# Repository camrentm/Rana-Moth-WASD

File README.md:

# The Rana Labs Moth (WASD Version)

WASD version of [Rana Labs'](https://github.com/rana-sylvatica) Moth, a foldable leverless controller.

<div style="display: flex; gap: 10px;">

</div>

---

## Components

I printed the entire shell and hinges in **Bambu Lab Matte PLA** (any PLA should work, though build quality feel may vary).

- **Mainboard:** RP2040 integrated directly onto the left custom PCB. The right side connects via ribbon cable.
- **Switches:** Any Kailh Choc low-profile switch. Must be low-profile (standard height switches won't fit).
- **USB-C:** [QuRB](https://github.com/rana-sylvatica/rana-tadpole/tree/main/PCBs/Breakout%20Board%20(QuRB)) by [Quark Works](https://github.com/quark-works) and Rana Labs, a USB-C breakout board with a ribbon cable port for solderless assembly.
- **Hardware:** M2 and M3 screws only. You'll need ten M3 heat inserts for the backplates, twelve M3×5/6mm bolts for the backplates and QuRB, and eight M2×4mm bolts for the mainboards.

---

## Assembly

The custom PCB eliminates all handwiring. The only soldering required is installing the hotswap sockets for the Choc switches.

The two halves connect via a 20-pin 0.5mm pitch ribbon cable. The QuRB connects to the left board via a 12-pin 0.5mm pitch ribbon cable for the USB-C port.

---

## Firmware

This build runs a custom fork of HayBox configured for the Moth layout. Find it at [camrentm/HayBox-Rana-Moth](https://github.com/camrentm/HayBox-Rana-Moth).

---

## Magnets

Strong magnets are essential since they're working against the spring force of every switch.

- **Size:** 6×3mm Neodymium, stacked 2 high per hole
- **Count:** 10 holes × 2 magnets = **20 magnets total**

The snap when closing is very satisfying and holds the Moth securely folded.

---

## Prism Ergonomic Mode

In the reverse-folded position, a lip on each hinge piece stops the wings from overfolding and creates a clean resting angle. The rounded hinge backs add friction to keep the Moth rigid in this position.

You can edit the lip width in the hinge model to adjust the fold angle to your preference.

---

## Notes

- **Button fit:** Buttons must sit flush with the face when depressed, or the halves won't close cleanly. Strong magnets may compensate for minor protrusion.
- **Hinge pin slot:** Left open in this design. The friction fit holds without caps, and it makes intentional pin removal much easier.

---

## Files

| Folder | Contents |
|--------|----------|
| `Shell/` | Top panels and backplates (STEP) |
| `Hinge and Buttons/` | Hinge upper/lower, hinge pin, and keycap models (STEP) |
| `Moth PCB/` | KiCad PCB project, schematics, and fabrication files |
| `DXF/` | PCB outlines and hole patterns |
| `Images/` | Build photos |

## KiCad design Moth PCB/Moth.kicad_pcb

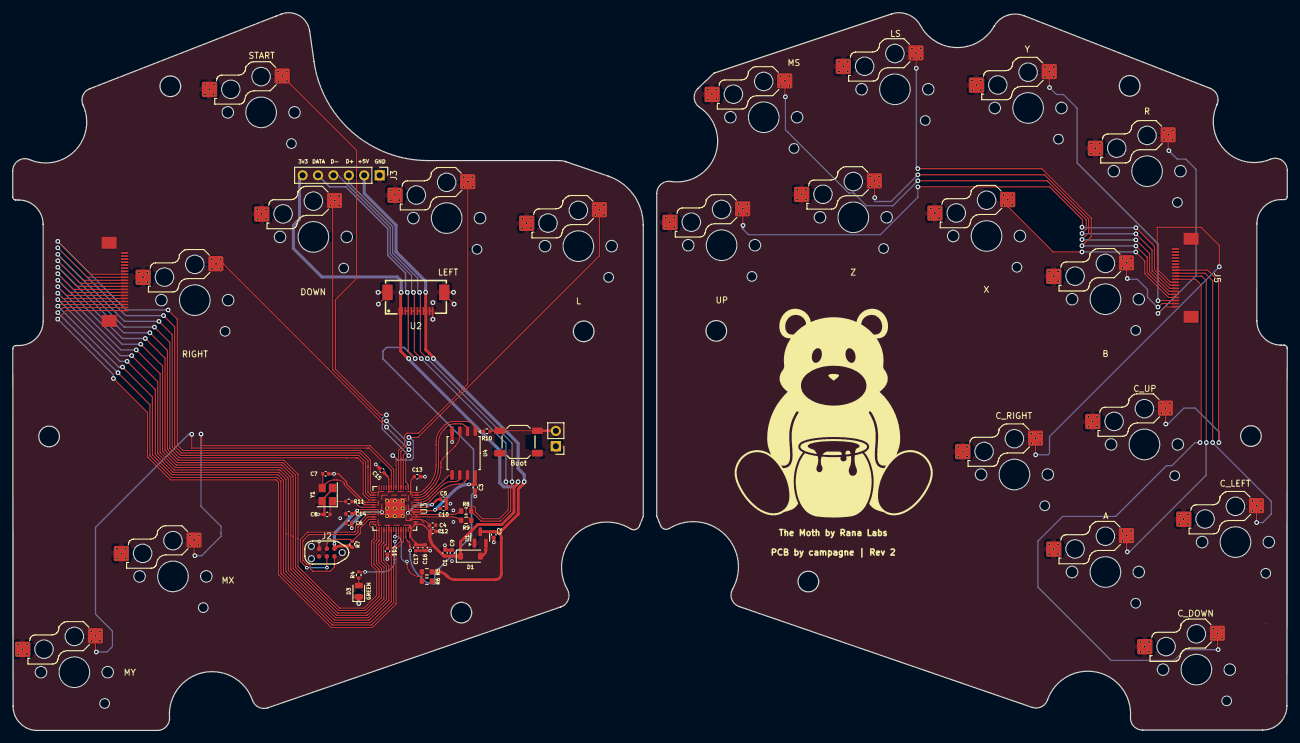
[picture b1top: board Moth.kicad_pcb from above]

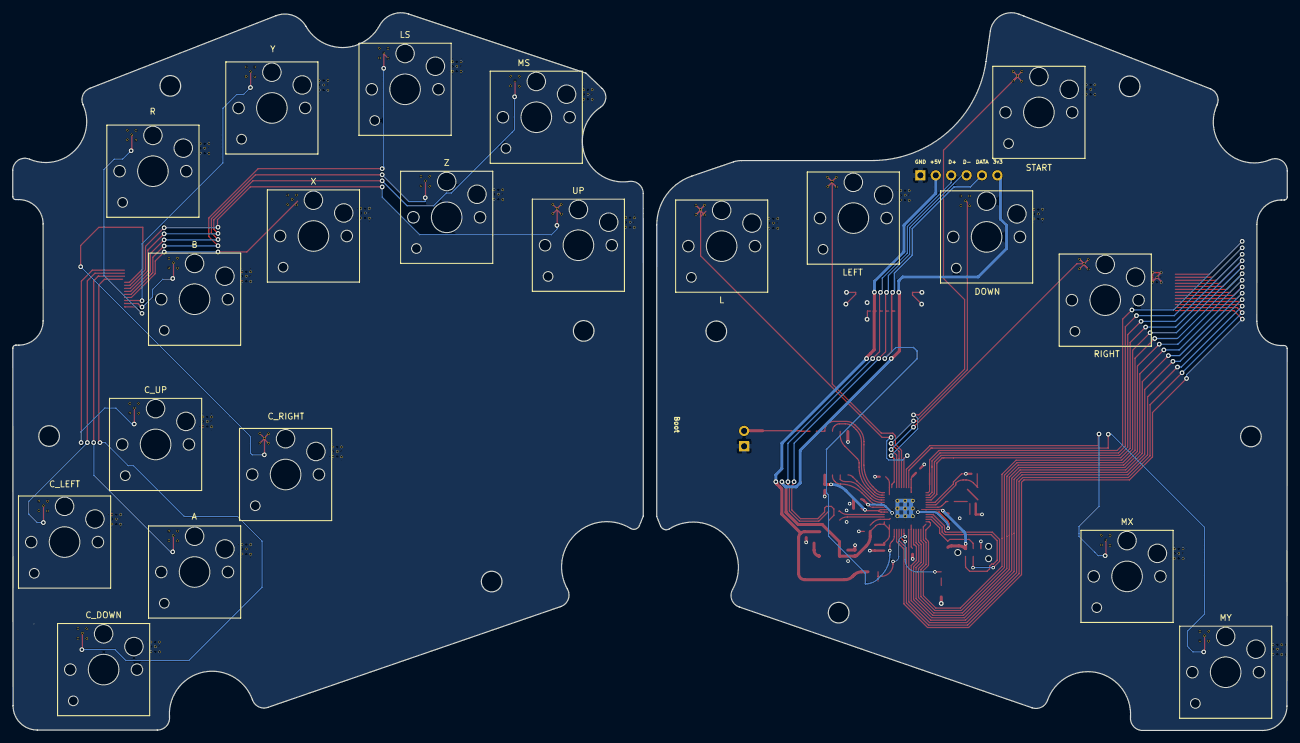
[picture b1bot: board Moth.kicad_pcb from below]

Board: 2 copper layers, 210.2 x 118.4 mm, 58 parts (20 on the bottom side), 59 nets.

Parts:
A: A; SW_Hotswap_Kailh_Choc_V1V2_THT
B: B; SW_Hotswap_Kailh_Choc_V1V2_THT
C1, C2, C4, C10: 1uF; C_0402_1005Metric
C3, C5, C6, C11, C12, C13, C14, C15, C16, C17: 100nF; C_0402_1005Metric
C7, C8: 22pF; C_0402_1005Metric
C9: 10uF; C_0402_1005Metric
C_DOWN: C Down; SW_Hotswap_Kailh_Choc_V1V2_THT
C_LEFT: C Left; SW_Hotswap_Kailh_Choc_V1V2_THT
C_RIGHT: C Right; SW_Hotswap_Kailh_Choc_V1V2_THT
C_UP: C Up; SW_Hotswap_Kailh_Choc_V1V2_THT
D1: Schottky Diode; D_SOD-123
D3: GREEN; LED_0805_2012Metric
DOWN: Down; SW_Hotswap_Kailh_Choc_V1V2_THT
J1: Conn_01x02; PinHeader_1x02_P2.54mm_Vertical
J2: JTAG_TC2030; CON_TC2030_outlined
J3: DuPont Connector; PinHeader_1x06_P2.54mm_Vertical
J4: Left Ribbon; FPC-05F-30PH20
J5: Right Ribbon; FPC-05F-30PH20
L: L; SW_Hotswap_Kailh_Choc_V1V2_THT
LEFT: Left; SW_Hotswap_Kailh_Choc_V1V2_THT
LS: LS; SW_Hotswap_Kailh_Choc_V1V2_THT
MS: MS; SW_Hotswap_Kailh_Choc_V1V2_THT
MX: MX; SW_Hotswap_Kailh_Choc_V1V2_THT
MY : MY; SW_Hotswap_Kailh_Choc_V1V2_THT
R: R; SW_Hotswap_Kailh_Choc_V1V2_THT
R4: 470; R_0402_1005Metric
R5: 5.6k; R_0603_1608Metric
R6: 10k; R_0603_1608Metric
R7: 10k; R_0402_1005Metric
R8, R9: 27; R_0603_1608Metric
R10, R11: 1k; R_0402_1005Metric
RIGHT: Right; SW_Hotswap_Kailh_Choc_V1V2_THT
START: Start; SW_Hotswap_Kailh_Choc_V1V2_THT
SW1: Boot; SW_SPST_SKQG_WithStem
U1: XC6206; SOT-23
U2: X05A26H12G; FPC-SMD_X05A26H12G
U3: RP2040; RP2040-QFN-56
U4: W25Q128JVS; SOIC-8_5.23x5.23mm_P1.27mm
UP: Up; SW_Hotswap_Kailh_Choc_V1V2_THT
X: X; SW_Hotswap_Kailh_Choc_V1V2_THT
Y: Y; SW_Hotswap_Kailh_Choc_V1V2_THT
Y1: 12MHz; Crystal_SMD_3225-4Pin_3.2x2.5mm
Z: Z; SW_Hotswap_Kailh_Choc_V1V2_THT

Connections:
3vDiode: C1.2, C3.1, C9.1, C10.1, C11.1, C12.1, C13.1, C14.1, C15.1, C16.1, C17.1, D1.1 (K), J2.1 (VCC), J3.6, R7.1, U2.1, U2.2, U3.1 (IOVDD), U3.10 (IOVDD), U3.22 (IOVDD), U3.33 (IOVDD), U3.42 (IOVDD), U3.43 (ADC_AVDD), U3.44 (VREG_VIN), U3.48 (USB_VDD), U3.49 (IOVDD), U4.8 (VCC)
+1V1: C4.1, C5.1, C6.1, U3.23 (DVDD), U3.45 (VREG_VOUT), U3.50 (DVDD)
+5V: C2.2, J3.2, R5.1, U1.3 (VI), U2.9, U2.10
/D_+: R8.2, U3.47 (D+)
/D_-: R9.2, U3.46 (D-)
/XTAL_O: C8.2, R11.1, Y1.1
/~USB_BOOT: J1.2, R10.1, SW1.2
A: A.1, J5.11
A RIBBON: J4.10, U3.17 (GPIO14)
B: B.1, J5.2
B RIBBON: J4.19, U3.38 (GPIO26/ADC0)
CS: R10.2, U3.56 (QSPI_SS_N), U4.1 (~CS)
C_DN: C_DOWN.1, J5.10
C_DN RIBBON: J4.11, U3.18 (GPIO15)
C_LT: C_LEFT.1, J5.12
C_LT RIBBON: J4.9, U3.16 (GPIO13)
C_RT: C_RIGHT.1, J5.9
C_RT RIBBON: J4.12, U3.27 (GPIO16)
C_UP: C_UP.1, J5.13
C_UP RIBBON: J4.8, U3.15 (GPIO12)
D+: J3.3, R8.1, U2.7, U2.8
D-: J3.4, R9.1, U2.5, U2.6
DATA: J3.5, U2.3, U2.4, U3.40 (GPIO28/ADC2)
DOWN: DOWN.1, U3.5 (GPIO3)
GND: A.2, B.2, C1.1, C2.1, C3.2, C4.2, C5.2, C6.2, C7.1, C8.1, C9.2, C10.2, C11.2, C12.2, C13.2, C14.2, C15.2, C16.2, C17.2, C_DOWN.2, C_LEFT.2, C_RIGHT.2, C_UP.2, D3.1 (K), DOWN.2, J1.1, J2.5 (GND), J3.1, J4.7, J5.14, L.2, LEFT.2, LS.2, MS.2, MX.2, MY.2, R.2, R6.2, RIGHT.2, START.2, SW1.1, U1.1 (GND), U2.11, U2.12, U2.13, U2.14, U3.19 (TESTEN), U3.57 (GND), U4.4 (GND), UP.2, X.2, Y.2, Y1.2, Y1.4, Z.2
L: L.1, U3.7 (GPIO5)
LEFT: LEFT.1, U3.6 (GPIO4)
LS: J5.5, LS.1
LS RIBBON: J4.16, U3.31 (GPIO20)
M1: MX.1, U3.8 (GPIO6)
M2: MY.1, U3.9 (GPIO7)
MS: J5.7, MS.1
MS RIBBON: J4.14, U3.29 (GPIO18)
unnamed: D1.2 (A), U1.2 (VO)
unnamed: D3.2 (A), R4.2
PICO_LED: R4.1, U3.37 (GPIO25)
QSPI_CLK: U3.52 (QSPI_SCLK), U4.6 (CLK)
R: J5.1, R.1
R RIBBON: J4.20, U3.39 (GPIO27/ADC1)
RIGHT: RIGHT.1, U3.4 (GPIO2)
SD0: U3.53 (QSPI_SD0), U4.5 (DI(IO0))
SD1: U3.55 (QSPI_SD1), U4.2 (DO(IO1))
SD2: U3.54 (QSPI_SD2), U4.3 (IO2)
SD3: U3.51 (QSPI_SD3), U4.7 (IO3)
START: START.1, U3.2 (GPIO0)
SWCLK: J2.4 (SWCLK), U3.24 (SWCLK)
SWD: J2.2 (SWDIO), U3.25 (SWDIO)
UP: J5.8, UP.1
UP RIBBON: J4.13, U3.28 (GPIO17)
VBUS_SENSE: R5.2, R6.1, U3.36 (GPIO24)
X: J5.4, X.1
X RIBBON: J4.17, U3.32 (GPIO21)
XTAL_IN: C7.2, U3.20 (XTAL_IN), Y1.3
XTAL_OUT: R11.2, U3.21 (XTAL_OUT)
Y: J5.3, Y.1
Y RIBBON: J4.18, U3.34 (GPIO22)
Z: J5.6, Z.1
Z RIBBON: J4.15, U3.30 (GPIO19)
~RESET: J2.3 (~RST), R7.2, U3.26 (~RUN)

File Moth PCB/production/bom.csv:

Designator,Footprint,Quantity,Value,LCSC Part #
A,SW_Hotswap_Kailh_Choc_V1V2_THT,1,A,
B,SW_Hotswap_Kailh_Choc_V1V2_THT,1,B,
"C1, C10, C2, C4",0402,4,1uF,C52923
"C11, C12, C13, C14, C15, C16, C17, C3, C5, C6",0402,10,100nF,C1525
"C7, C8",0402,2,22pF,C1555
C9,0402,1,10uF,C15525
C_DOWN,SW_Hotswap_Kailh_Choc_V1V2_THT,1,C Down,
C_LEFT,SW_Hotswap_Kailh_Choc_V1V2_THT,1,C Left,
C_RIGHT,SW_Hotswap_Kailh_Choc_V1V2_THT,1,C Right,
C_UP,SW_Hotswap_Kailh_Choc_V1V2_THT,1,C Up,
D1,D_SOD-123,1,Schottky Diode,C8598
D3,0805,1,GREEN,C84256
DOWN,SW_Hotswap_Kailh_Choc_V1V2_THT,1,Down,
J4,FPC-05F-30PH20,1,Left Ribbon,
J5,FPC-05F-30PH20,1,Right Ribbon,
L,SW_Hotswap_Kailh_Choc_V1V2_THT,1,L,
LEFT,SW_Hotswap_Kailh_Choc_V1V2_THT,1,Left,
LS,SW_Hotswap_Kailh_Choc_V1V2_THT,1,LS,
MS,SW_Hotswap_Kailh_Choc_V1V2_THT,1,MS,
MX,SW_Hotswap_Kailh_Choc_V1V2_THT,1,MX,
MY ,SW_Hotswap_Kailh_Choc_V1V2_THT,1,MY,
R,SW_Hotswap_Kailh_Choc_V1V2_THT,1,R,
"R10, R11",0402,2,1k,C11702
R4,0402,1,470,C25117
R5,0603,1,5.6k,C23189
R6,0603,1,10k,C25804
R7,0402,1,10k,C25744
"R8, R9",0603,2,27,C25190
RIGHT,SW_Hotswap_Kailh_Choc_V1V2_THT,1,Right,
START,SW_Hotswap_Kailh_Choc_V1V2_THT,1,Start,
SW1,SW_SPST_SKQG_WithStem,1,Boot,C202424
U1,SOT-23,1,XC6206,C5446
U2,FPC-SMD_X05A26H12G,1,X05A26H12G,C519263
U3,RP2040-QFN-56,1,RP2040,C2040
U4,SOIC-8_5.23x5.23mm_P1.27mm,1,W25Q128JVS,C97521
UP,SW_Hotswap_Kailh_Choc_V1V2_THT,1,Up,
X,SW_Hotswap_Kailh_Choc_V1V2_THT,1,X,
Y,SW_Hotswap_Kailh_Choc_V1V2_THT,1,Y,
Y1,Crystal_SMD_3225-4Pin_3.2x2.5mm,1,12MHz,C9002
Z,SW_Hotswap_Kailh_Choc_V1V2_THT,1,Z,
